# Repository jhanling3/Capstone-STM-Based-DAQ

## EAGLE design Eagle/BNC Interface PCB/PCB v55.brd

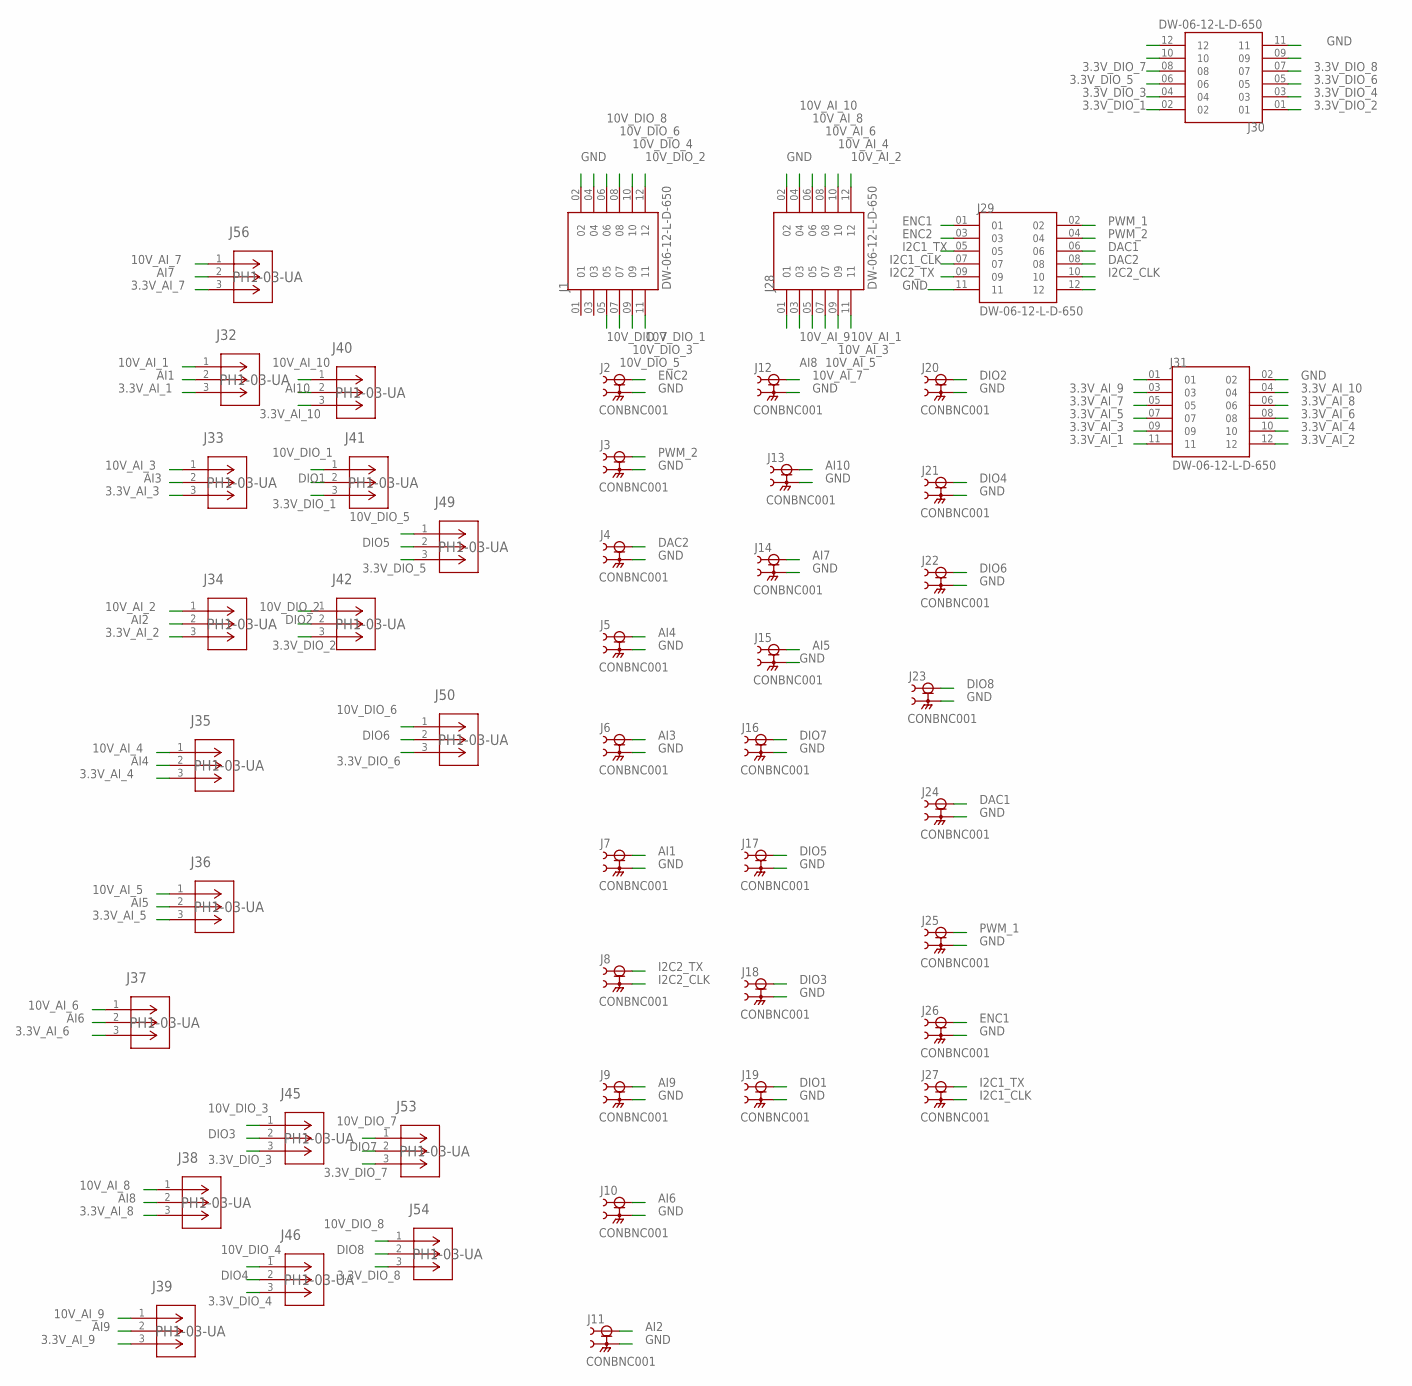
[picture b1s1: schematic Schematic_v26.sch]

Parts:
J1, J28, J29, J30, J31: DW-06-12-L-D-650; SAMTEC_DW-06-12-L-D-650
J2, J3, J4, J5, J6, J7, J8, J9, J10, J11, J12, J13, J14, J15, J16, J17, J18, J19, J20, J21, J22, J23, J24, J25, J26, J27: CONBNC001; LINX_CONBNC001
J32, J33, J34, J35, J36, J37, J38, J39, J40, J41, J42, J45, J46, J49, J50, J53, J54, J56: PH1-03-UA; CONN_PH1-03-UA_ADM

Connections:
3.3V_AI_1: J31.11, J32.3
3.3V_AI_2: J31.12, J34.3
3.3V_AI_3: J31.09, J33.3
3.3V_AI_4: J31.10, J35.3
3.3V_AI_5: J31.07, J36.3
3.3V_AI_6: J31.08, J37.3
3.3V_AI_7: J31.05, J56.3
3.3V_AI_8: J31.06, J38.3
3.3V_AI_9: J31.03, J39.3
3.3V_AI_10: J31.04, J40.3
3.3V_DIO_1: J30.02, J41.3
3.3V_DIO_2: J30.01, J42.3
3.3V_DIO_3: J30.04, J45.3
3.3V_DIO_4: J30.03, J46.3
3.3V_DIO_5: J30.06, J49.3
3.3V_DIO_6: J30.05, J50.3
3.3V_DIO_7: J30.08, J53.3
3.3V_DIO_8: J30.07, J54.3
10V_AI_1: J28.11, J32.1
10V_AI_2: J28.12, J34.1
10V_AI_3: J28.09, J33.1
10V_AI_4: J28.10, J35.1
10V_AI_5: J28.07, J36.1
10V_AI_6: J28.08, J37.1
10V_AI_7: J28.05, J56.1
10V_AI_8: J28.06, J38.1
10V_AI_9: J28.03, J39.1
10V_AI_10: J28.04, J40.1
10V_DIO_1: J1.11, J41.1
10V_DIO_2: J1.12, J42.1
10V_DIO_3: J1.09, J45.1
10V_DIO_4: J1.10, J46.1
10V_DIO_5: J1.07, J49.1
10V_DIO_6: J1.08, J50.1
10V_DIO_7: J1.05, J53.1
10V_DIO_8: J1.06, J54.1
AI1: J7.1, J32.2
AI2: J11.1, J34.2
AI3: J6.1, J33.2
AI4: J5.1, J35.2
AI5: J15.1, J36.2
AI6: J10.1, J37.2
AI7: J14.1, J56.2
AI8: J12.1, J38.2
AI9: J9.1, J39.2
AI10: J13.1, J40.2
DAC1: J24.1, J29.06
DAC2: J4.1, J29.08
DIO1: J19.1, J41.2
DIO2: J20.1, J42.2
DIO3: J18.1, J45.2
DIO4: J21.1, J46.2
DIO5: J17.1, J49.2
DIO6: J22.1, J50.2
DIO7: J16.1, J53.2
DIO8: J23.1, J54.2
ENC1: J26.1, J29.01
ENC2: J2.1, J29.03
GND: J1.02, J2.S1 (2), J2.S2 (2), J2.S3 (2), J2.S4 (2), J3.S1 (2), J3.S2 (2), J3.S3 (2), J3.S4 (2), J4.S1 (2), J4.S2 (2), J4.S3 (2), J4.S4 (2), J5.S1 (2), J5.S2 (2), J5.S3 (2), J5.S4 (2), J6.S1 (2), J6.S2 (2), J6.S3 (2), J6.S4 (2), J7.S1 (2), J7.S2 (2), J7.S3 (2), J7.S4 (2), J9.S1 (2), J9.S2 (2), J9.S3 (2), J9.S4 (2), J10.S1 (2), J10.S2 (2), J10.S3 (2), J10.S4 (2), J11.S1 (2), J11.S2 (2), J11.S3 (2), J11.S4 (2), J12.S1 (2), J12.S2 (2), J12.S3 (2), J12.S4 (2), J13.S1 (2), J13.S2 (2), J13.S3 (2), J13.S4 (2), J14.S1 (2), J14.S2 (2), J14.S3 (2), J14.S4 (2), J15.S1 (2), J15.S2 (2), J15.S3 (2), J15.S4 (2), J16.S1 (2), J16.S2 (2), J16.S3 (2), J16.S4 (2), J17.S1 (2), J17.S2 (2), J17.S3 (2), J17.S4 (2), J18.S1 (2), J18.S2 (2), J18.S3 (2), J18.S4 (2), J19.S1 (2), J19.S2 (2), J19.S3 (2), J19.S4 (2), J20.S1 (2), J20.S2 (2), J20.S3 (2), J20.S4 (2), J21.S1 (2), J21.S2 (2), J21.S3 (2), J21.S4 (2), J22.S1 (2), J22.S2 (2), J22.S3 (2), J22.S4 (2), J23.S1 (2), J23.S2 (2), J23.S3 (2), J23.S4 (2), J24.S1 (2), J24.S2 (2), J24.S3 (2), J24.S4 (2), J25.S1 (2), J25.S2 (2), J25.S3 (2), J25.S4 (2), J26.S1 (2), J26.S2 (2), J26.S3 (2), J26.S4 (2), J28.02, J29.11, J30.11, J31.02
I2C1_CLK: J27.S1 (2), J27.S2 (2), J27.S3 (2), J27.S4 (2), J29.07
I2C1_TX: J27.1, J29.05
I2C2_CLK: J8.S1 (2), J8.S2 (2), J8.S3 (2), J8.S4 (2), J29.10
I2C2_TX: J8.1, J29.09
PWM_1: J25.1, J29.02
PWM_2: J3.1, J29.04

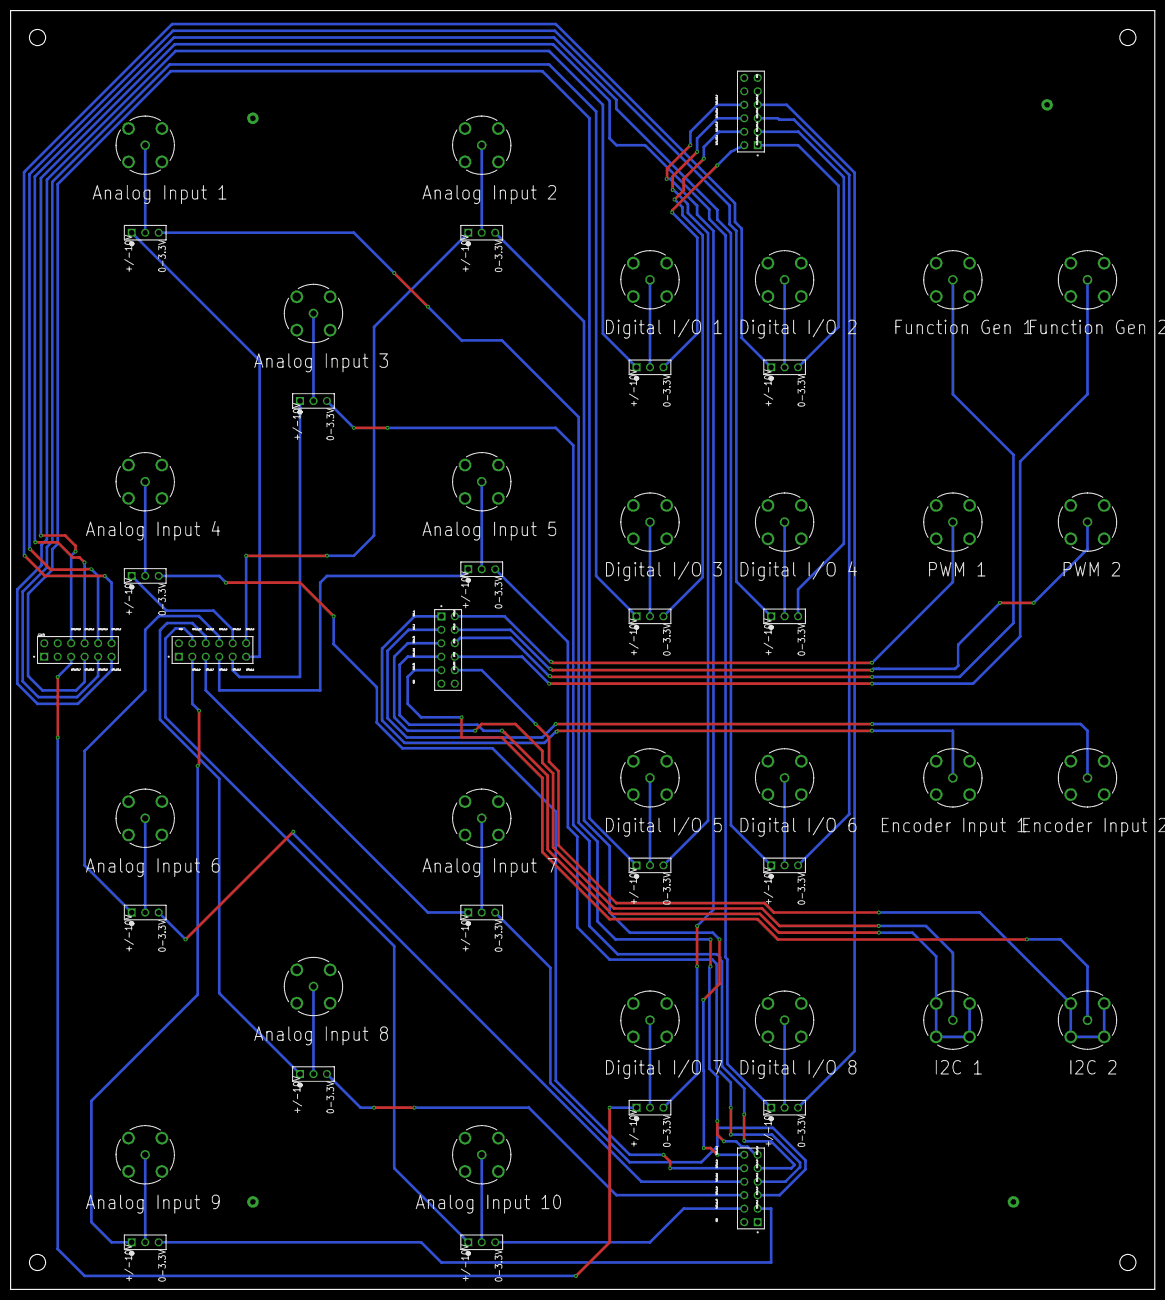
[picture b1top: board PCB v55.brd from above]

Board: 2 copper layers, 215.9 x 241.3 mm, 49 parts (0 on the bottom side), 65 nets.

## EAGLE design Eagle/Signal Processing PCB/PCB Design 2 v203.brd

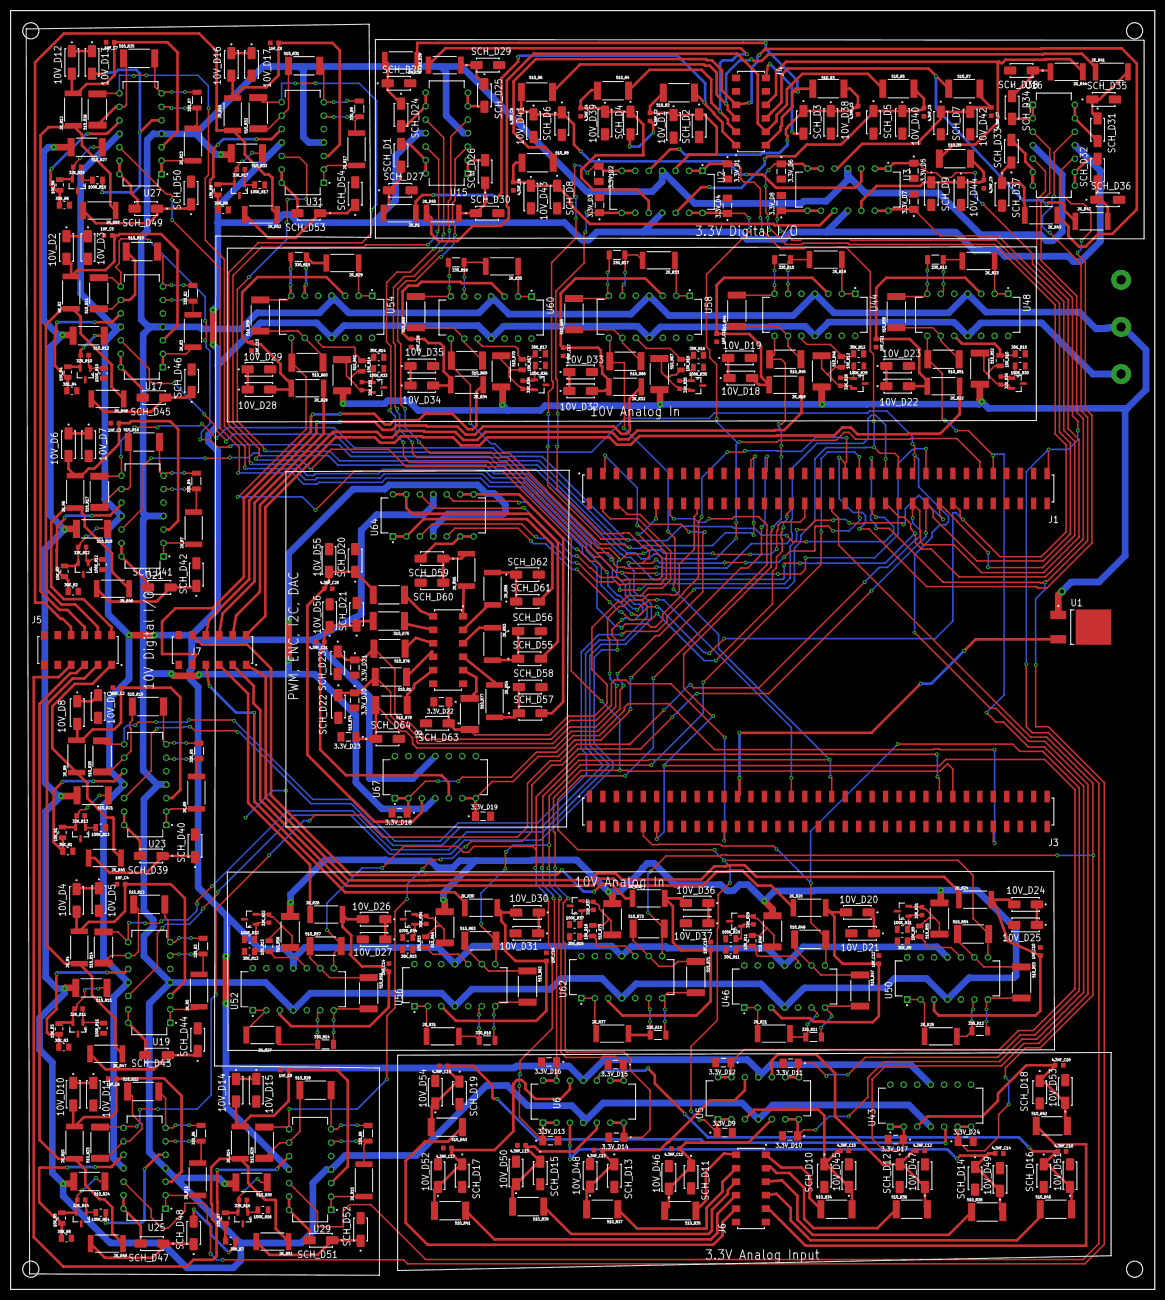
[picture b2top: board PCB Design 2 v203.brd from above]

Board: 2 copper layers, 215.9 x 241.3 mm, 459 parts (0 on the bottom side), 308 nets.

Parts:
1NF_C2, 1NF_C3, 1NF_C4, 1NF_C5, 1NF_C6, 1NF_C7, 1NF_C8, 1NF_C9, 1NF_C10, 1NF_C11, 1NF_C12, 1NF_C13, 1NF_C14, 1NF_C15, 1NF_C16, 1NF_C17, 1NF_C18, 1NF_C19: GRM1885C1H102JA01D; CAPC1608X90N
2K_R1, 2K_R2, 2K_R3, 2K_R4, 2K_R5, 2K_R6, 2K_R7, 2K_R8, 2K_R9, 2K_R10, 2K_R11, 2K_R12, 2K_R13, 2K_R14, 2K_R15, 2K_R16, 2K_R17, 2K_R18, 2K_R19, 2K_R20, 2K_R21, 2K_R22, 2K_R23, 2K_R24, 2K_R25, 2K_R26, 2K_R27, 2K_R28, 2K_R29, 2K_R30, 2K_R31, 2K_R32, 2K_R33, 2K_R34, 2K_R35, 2K_R36, 2K_R37, 2K_R38, 2K_R39, 2K_R40, 2K_R41, 2K_R42, 2K_R43, 2K_R44, 2K_R45, 2K_R46, 2K_R47, 2K_R48, 2K_R49, 2K_R50, 2K_R51, 2K_R52, 2K_R53, 2K_R54, 2K_R55, 2K_R56: RC2512FK-072KL; RESC6331X65N
3.3V_D1, 3.3V_D2, 3.3V_D3, 3.3V_D4, 3.3V_D5, 3.3V_D6, 3.3V_D7, 3.3V_D8, 3.3V_D9, 3.3V_D10, 3.3V_D11, 3.3V_D12, 3.3V_D13, 3.3V_D14, 3.3V_D15, 3.3V_D16, 3.3V_D17, 3.3V_D18, 3.3V_D19, 3.3V_D20, 3.3V_D21, 3.3V_D22, 3.3V_D23, 3.3V_D24: BZT52B3V3_RHG; DIO_BZT52B3V3_RHG
4.3NF_C2, 4.3NF_C3, 4.3NF_C4, 4.3NF_C5, 4.3NF_C6, 4.3NF_C7, 4.3NF_C8, 4.3NF_C9, 4.3NF_C10, 4.3NF_C11, 4.3NF_C12, 4.3NF_C13, 4.3NF_C14, 4.3NF_C15, 4.3NF_C16, 4.3NF_C17, 4.3NF_C18, 4.3NF_C19, 4.3NF_C20, 4.3NF_C21: GRM1885C1H432JA01D; CAPC1608X90N
10K_R1, 10K_R2, 10K_R3, 10K_R4, 10K_R5, 10K_R6, 10K_R7, 10K_R8, 10K_R9, 10K_R10, 10K_R11, 10K_R12, 10K_R13, 10K_R14, 10K_R15, 10K_R16, 10K_R17, 10K_R18: RCS080510K0FKEA; RESC2012X50N
10V_D1, 10V_D2, 10V_D3, 10V_D4, 10V_D5, 10V_D6, 10V_D7, 10V_D8, 10V_D9, 10V_D10, 10V_D11, 10V_D12, 10V_D13, 10V_D14, 10V_D15, 10V_D16, 10V_D17, 10V_D18, 10V_D19, 10V_D20, 10V_D21, 10V_D22, 10V_D23, 10V_D24, 10V_D25, 10V_D26, 10V_D27, 10V_D28, 10V_D29, 10V_D30, 10V_D31, 10V_D32, 10V_D33, 10V_D34, 10V_D35, 10V_D36, 10V_D37, 10V_D38, 10V_D39, 10V_D40, 10V_D41, 10V_D42, 10V_D43, 10V_D44, 10V_D45, 10V_D46, 10V_D47, 10V_D48, 10V_D49, 10V_D50, 10V_D51, 10V_D52, 10V_D53, 10V_D54, 10V_D55, 10V_D56: SMAZ10-13-F; DIOM5226X240N
30K_R1, 30K_R2, 30K_R3, 30K_R4, 30K_R5, 30K_R6, 30K_R7, 30K_R8, 30K_R9, 30K_R10, 30K_R11, 30K_R12, 30K_R13, 30K_R14, 30K_R15, 30K_R16, 30K_R17, 30K_R18: RMCF0805FT30K0; RESC2012X65N
32K_R10, 32K_R11, 32K_R12, 32K_R13, 32K_R14, 32K_R15, 32K_R16, 32K_R17, 32K_R28, 32K_R29, 32K_R30, 32K_R31, 32K_R32, 32K_R33, 32K_R34, 32K_R35, 32K_R36, 32K_R37: RNCF0603BTE32K0; RESC1508X55N
100K_R10, 100K_R11, 100K_R12, 100K_R13, 100K_R14, 100K_R15, 100K_R16, 100K_R17, 100K_R28, 100K_R29, 100K_R30, 100K_R31, 100K_R32, 100K_R33, 100K_R34, 100K_R35, 100K_R36, 100K_R37: RC0805FR-07100KL; RESC2012X60N
330_R2, 330_R3, 330_R4, 330_R5, 330_R6, 330_R7, 330_R8, 330_R9, 330_R10, 330_R11, 330_R12, 330_R13, 330_R14, 330_R15, 330_R16, 330_R17, 330_R18, 330_R19: RC1206FR-07330RL; RESC3116X65N
510_R1, 510_R2, 510_R3, 510_R4, 510_R5, 510_R6, 510_R7, 510_R8, 510_R9, 510_R10, 510_R11, 510_R12, 510_R13, 510_R14, 510_R15, 510_R16, 510_R17, 510_R18, 510_R19, 510_R20, 510_R21, 510_R22, 510_R23, 510_R24, 510_R25, 510_R26, 510_R27, 510_R28, 510_R29, 510_R30, 510_R31, 510_R32, 510_R33, 510_R34, 510_R35, 510_R36, 510_R37, 510_R38, 510_R39, 510_R40, 510_R41, 510_R42, 510_R43, 510_R44, 510_R45, 510_R46, 510_R47, 510_R48, 510_R49, 510_R50, 510_R51, 510_R52, 510_R53, 510_R54, 510_R55, 510_R56, 510_R57, 510_R58, 510_R59, 510_R60, 510_R61, 510_R62, 510_R63, 510_R64, 510_R65, 510_R66, 510_R67, 510_R68, 510_R69, 510_R70, 510_R71, 510_R72, 510_R73, 510_R74, 510_R75, 510_R76, 510_R77, 510_R78: RMCF2512FT510R; RESC6332X70N
J1, J3: SSM-135-L-DV; SAMTEC_SSM-135-L-DV
J4, J5, J6, J7, J8: 89898-306ALF; AMPHENOL_89898-306ALF
SCH_D1, SCH_D2, SCH_D3, SCH_D4, SCH_D5, SCH_D6, SCH_D7, SCH_D8, SCH_D9, SCH_D10, SCH_D11, SCH_D12, SCH_D13, SCH_D14, SCH_D15, SCH_D16, SCH_D17, SCH_D18, SCH_D19, SCH_D20, SCH_D21, SCH_D22, SCH_D23, SCH_D24, SCH_D25, SCH_D26, SCH_D27, SCH_D28, SCH_D29, SCH_D30, SCH_D31, SCH_D32, SCH_D33, SCH_D34, SCH_D35, SCH_D36, SCH_D37, SCH_D38, SCH_D39, SCH_D40, SCH_D41, SCH_D42, SCH_D43, SCH_D44, SCH_D45, SCH_D46, SCH_D47, SCH_D48, SCH_D49, SCH_D50, SCH_D51, SCH_D52, SCH_D53, SCH_D54, SCH_D55, SCH_D56, SCH_D57, SCH_D58, SCH_D59, SCH_D60, SCH_D61, SCH_D62, SCH_D63, SCH_D64: B140-13-F; DIOM4326X240N
U1: L78M08CDT-TR; VREG_L78M08CDT-TR
U2, U3, U5, U6, U15, U16, U17, U19, U21, U23, U25, U27, U29, U31, U43, U44, U46, U48, U50, U52, U54, U56, U58, U60, U62, U64, U67: TL074IN; DIP794W45P254L1969H508Q14
U18, U20, U22, U24, U26, U28, U30, U32, U45, U47, U49, U51, U53, U55, U57, U59, U61, U63: TL431AIDBZR; SOT95P237X112-3N

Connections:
3.3_AI_1: 510_R34.1, J6.01
3.3_AI_2: 510_R35.1, J6.02
3.3_AI_3: 510_R36.1, J6.03
3.3_AI_4: 510_R37.1, J6.04
3.3_AI_5: 510_R38.1, J6.05
3.3_AI_6: 510_R39.1, J6.06
3.3_AI_7: 510_R40.1, J6.07
3.3_AI_8: 510_R41.1, J6.08
3.3_AI_9: 510_R42.1, J6.09
3.3_AI_10: 510_R43.1, J6.10
10V_AI_1: 2K_R24.1, J7.01
10V_AI_2: 2K_R22.1, J7.02
10V_AI_3: 2K_R20.1, J7.03
10V_AI_4: 2K_R18.1, J7.04
10V_AI_5: 2K_R26.1, J7.05
10V_AI_6: 2K_R28.1, J7.06
10V_AI_7: 2K_R30.1, J7.07
10V_AI_8: 2K_R32.1, J7.08
10V_AI_9: 2K_R34.1, J7.09
10V_AI_10: 2K_R36.1, J7.10
10V_DIO_1: 2K_R8.1, 2K_R45.1, J5.01
10V_DIO_1_PRE: SCH_D39.A, U23.13, U23.14
10V_DIO_2: 2K_R6.1, 2K_R46.1, J5.02
10V_DIO_3: 2K_R4.1, 2K_R47.1, J5.03
10V_DIO_3_PRE: SCH_D43.A, U19.13, U19.14
10V_DIO_4: 2K_R2.1, 2K_R48.1, J5.04
10V_DIO_4_PRE: SCH_D45.A, U17.13, U17.14
10V_DIO_5: 2K_R10.1, 2K_R49.1, J5.05
10V_DIO_5_PRE: SCH_D47.A, U25.13, U25.14
10V_DIO_6: 2K_R12.1, 2K_R50.1, J5.06
10V_DIO_6_PRE: SCH_D49.A, U27.13, U27.14
10V_DIO_7: 2K_R14.1, 2K_R51.1, J5.07
10V_DIO_7_PRE: SCH_D51.A, U29.13, U29.14
10V_DIO_8: 2K_R16.1, 2K_R52.1, J5.08
10V_DIO_8_PRE: SCH_D53.A, U31.13, U31.14
10V_DIO_PRE: SCH_D41.A, U21.13, U21.14
+V: 510_R12.2, 510_R15.2, 510_R18.2, 510_R21.2, 510_R24.2, 510_R27.2, 510_R30.2, 510_R33.2, 510_R46.2, 510_R49.2, 510_R52.2, 510_R55.2, 510_R58.2, 510_R61.2, 510_R64.2, 510_R67.2, 510_R70.2, 510_R73.2, U1.1, U2.4, U3.4, U5.4, U6.4, U15.4, U16.4, U17.4, U19.4, U21.4, U23.4, U25.4, U27.4, U29.4, U31.4, U43.4, U44.4, U46.4, U48.4, U50.4, U52.4, U54.4, U56.4, U58.4, U60.4, U62.4, U64.4, U67.4
-V: U2.11, U3.11, U5.11, U6.11, U15.11, U16.11, U17.11, U19.11, U21.11, U23.11, U25.11, U27.11, U29.11, U31.11, U43.11, U44.11, U46.11, U48.11, U50.11, U52.11, U54.11, U56.11, U58.11, U60.11, U62.11, U64.11, U67.11
AI_AMP_1: 4.3NF_C10.1, 10V_D45.1, 510_R34.2, SCH_D10.C, U5.3
AI_AMP_2: 4.3NF_C11.1, 10V_D46.1, 510_R35.2, SCH_D11.C, U5.5
AI_AMP_3: 4.3NF_C12.1, 10V_D47.1, 510_R36.2, SCH_D12.C, U5.10
AI_AMP_4: 4.3NF_C13.1, 10V_D48.1, 510_R37.2, SCH_D13.C, U5.12
AI_AMP_5: 4.3NF_C14.1, 10V_D49.1, 510_R38.2, SCH_D14.C, U6.3
AI_AMP_6: 4.3NF_C15.1, 10V_D50.1, 510_R39.2, SCH_D15.C, U6.5
AI_AMP_7: 4.3NF_C16.1, 10V_D51.1, 510_R40.2, SCH_D16.C, U6.10
AI_AMP_8: 4.3NF_C17.1, 10V_D52.1, 510_R41.2, SCH_D17.C, U6.12
AI_AMP_9: 4.3NF_C18.1, 10V_D53.1, 510_R42.2, SCH_D18.C, U43.3
AI_AMP_10: 4.3NF_C19.1, 10V_D54.1, 510_R43.2, SCH_D19.C, U43.5
DAC1: 2K_R53.1, J8.05
DAC1_T: SCH_D57.A, U64.8, U64.9
DAC2: 2K_R54.1, J8.07
DAC2_T: SCH_D55.A, U64.13, U64.14
DIO_1: 2K_R1.1, 510_R2.1, J4.01
DIO_1_T: SCH_D1.A, U15.13, U15.14
DIO_2: 2K_R38.1, 510_R3.1, J4.02
DIO_2_T: SCH_D24.A, U15.8, U15.9
DIO_3: 2K_R39.1, 510_R4.1, J4.03
DIO_3_T: SCH_D25.A, U15.6, U15.7
DIO_4: 2K_R40.1, 510_R5.1, J4.04
DIO_4_T: SCH_D26.A, U15.1, U15.2
DIO_5: 2K_R41.1, 510_R6.1, J4.05
DIO_5_T: SCH_D31.A, U16.13, U16.14
DIO_6: 2K_R42.1, 510_R7.1, J4.06
DIO_6_T: SCH_D32.A, U16.8, U16.9
DIO_7: 2K_R43.1, 510_R8.1, J4.07
DIO_7_T: SCH_D33.A, U16.6, U16.7
DIO_8: 2K_R44.1, 510_R9.1, J4.08
DIO_8_T: SCH_D34.A, U16.1, U16.2
DIO_AMP_1: 4.3NF_C2.1, 10V_D1.1, 510_R2.2, SCH_D2.C, U2.3
DIO_AMP_2: 4.3NF_C3.1, 10V_D38.1, 510_R3.2, SCH_D3.C, U2.5
DIO_AMP_3: 4.3NF_C4.1, 10V_D39.1, 510_R4.2, SCH_D4.C, U2.10
DIO_AMP_4: 4.3NF_C5.1, 10V_D40.1, 510_R5.2, SCH_D5.C, U2.12
DIO_AMP_5: 4.3NF_C6.1, 10V_D41.1, 510_R6.2, SCH_D6.C, U3.3
DIO_AMP_6: 4.3NF_C7.1, 10V_D42.1, 510_R7.2, SCH_D7.C, U3.5
DIO_AMP_7: 4.3NF_C8.1, 10V_D43.1, 510_R8.2, SCH_D8.C, U3.10
DIO_AMP_8: 4.3NF_C9.1, 10V_D44.1, 510_R9.2, SCH_D9.C, U3.12
ENC_1: 510_R74.1, J8.02
ENC_2: 510_R75.1, J8.04
ENC_AMP_1: 4.3NF_C20.1, 10V_D55.1, 510_R74.2, SCH_D20.C, U67.3
ENC_AMP_2: 4.3NF_C21.1, 10V_D56.1, 510_R75.2, SCH_D21.C, U67.5
GND: 1NF_C2.2, 1NF_C3.2, 1NF_C4.2, 1NF_C5.2, 1NF_C6.2, 1NF_C7.2, 1NF_C8.2, 1NF_C9.2, 1NF_C10.2, 1NF_C11.2, 1NF_C12.2, 1NF_C13.2, 1NF_C14.2, 1NF_C15.2, 1NF_C16.2, 1NF_C17.2, 1NF_C18.2, 1NF_C19.2, 3.3V_D1.A, 3.3V_D2.A, 3.3V_D3.A, 3.3V_D4.A, 3.3V_D5.A, 3.3V_D6.A, 3.3V_D7.A, 3.3V_D8.A, 3.3V_D9.A, 3.3V_D10.A, 3.3V_D11.A, 3.3V_D12.A, 3.3V_D13.A, 3.3V_D14.A, 3.3V_D15.A, 3.3V_D16.A, 3.3V_D17.A, 3.3V_D18.A, 3.3V_D19.A, 3.3V_D20.A, 3.3V_D21.A, 3.3V_D22.A, 3.3V_D23.A, 3.3V_D24.A, 4.3NF_C2.2, 4.3NF_C3.2, 4.3NF_C4.2, 4.3NF_C5.2, 4.3NF_C6.2, 4.3NF_C7.2, 4.3NF_C8.2, 4.3NF_C9.2, 4.3NF_C10.2, 4.3NF_C11.2, 4.3NF_C12.2, 4.3NF_C13.2, 4.3NF_C14.2, 4.3NF_C15.2, 4.3NF_C16.2, 4.3NF_C17.2, 4.3NF_C18.2, 4.3NF_C19.2, 4.3NF_C20.2, 4.3NF_C21.2, 10V_D1.2, 10V_D3.2, 10V_D5.2, 10V_D7.2, 10V_D9.2, 10V_D11.2, 10V_D13.2, 10V_D15.2, 10V_D17.2, 10V_D19.2, 10V_D21.2, 10V_D23.2, 10V_D25.2, 10V_D27.2, 10V_D29.2, 10V_D31.2, 10V_D33.2, 10V_D35.2, 10V_D37.2, 10V_D38.2, 10V_D39.2, 10V_D40.2, 10V_D41.2, 10V_D42.2, 10V_D43.2, 10V_D44.2, 10V_D45.2, 10V_D46.2, 10V_D47.2, 10V_D48.2, 10V_D49.2, 10V_D50.2, 10V_D51.2, 10V_D52.2, 10V_D53.2, 10V_D54.2, 10V_D55.2, 10V_D56.2, 30K_R1.2, 30K_R2.2, 30K_R3.2, 30K_R4.2, 30K_R5.2, 30K_R6.2, 30K_R7.2, 30K_R8.2, 30K_R9.2, 30K_R10.2, 30K_R11.2, 30K_R12.2, 30K_R13.2, 30K_R14.2, 30K_R15.2, 30K_R16.2, 30K_R17.2, 30K_R18.2, 100K_R10.1, 100K_R11.1, 100K_R12.1, 100K_R13.1, 100K_R14.1, 100K_R15.1, 100K_R16.1, 100K_R17.1, 100K_R28.1, 100K_R29.1, 100K_R30.1, 100K_R31.1, 100K_R32.1, 100K_R33.1, 100K_R34.1, 100K_R35.1, 100K_R36.1, 100K_R37.1, J1.10, J1.19, J1.40, J1.53, J1.64, J3.07, J3.19, J3.20, J3.21, J3.50, J3.59, J4.12, J5.12, J6.12, J7.12, J8.12, SCH_D2.A, SCH_D3.A, SCH_D4.A, SCH_D5.A, SCH_D6.A, SCH_D7.A, SCH_D8.A, SCH_D9.A, SCH_D10.A, SCH_D11.A, SCH_D12.A, SCH_D13.A, SCH_D14.A, SCH_D15.A, SCH_D16.A, SCH_D17.A, SCH_D18.A, SCH_D19.A, SCH_D20.A, SCH_D21.A, SCH_D22.A, SCH_D23.A, SCH_D27.A, SCH_D28.A, SCH_D29.A, SCH_D30.A, SCH_D35.A, SCH_D36.A, SCH_D37.A, SCH_D38.A, SCH_D40.A, SCH_D42.A, SCH_D44.A, SCH_D46.A, SCH_D48.A, SCH_D50.A, SCH_D52.A, SCH_D54.A, SCH_D56.A, SCH_D58.A, SCH_D60.A, SCH_D62.A, SCH_D63.A, SCH_D64.A, U1.2, U17.5, U18.3, U19.5, U20.3, U21.5, U22.3, U23.5, U24.3, U25.5, U26.3, U27.5, U28.3, U29.5, U30.3, U31.5, U32.3, U44.5, U45.3, U46.5, U47.3, U48.5, U49.3, U50.5, U51.3, U52.5, U53.3, U54.5, U55.3, U56.5, U57.3, U58.5, U59.3, U60.5, U61.3, U62.5, U63.3
I2C1_CLK: 510_R1.1, J8.08
I2C1_TX: 510_R76.1, J8.06
I2C2_CLK: 510_R77.1, J8.09
I2C2_TX: 510_R78.1, J8.10
unnamed: 2K_R1.2, SCH_D1.C, SCH_D27.C
unnamed: 2K_R38.2, SCH_D24.C, SCH_D28.C
unnamed: 2K_R39.2, SCH_D25.C, SCH_D29.C
unnamed: 2K_R40.2, SCH_D26.C, SCH_D30.C
unnamed: 2K_R41.2, SCH_D31.C, SCH_D35.C
unnamed: 1NF_C5.1, 2K_R2.2, 10V_D2.2, U17.3
unnamed: 10V_D2.1, 10V_D3.1
unnamed: 2K_R43.2, SCH_D33.C, SCH_D37.C
unnamed: 2K_R3.1, U17.1, U17.2
unnamed: 2K_R44.2, SCH_D34.C, SCH_D38.C
unnamed: 2K_R42.2, SCH_D32.C, SCH_D36.C
unnamed: 510_R10.1, 510_R11.1, U17.9
unnamed: 330_R2.2, 510_R10.2, U17.7
unnamed: 2K_R3.2, 330_R2.1, U17.6
unnamed: 32K_R10.1, 100K_R10.2, U18.1
unnamed: 10K_R5.2, 32K_R14.2, 510_R24.1, U26.2
unnamed: 1NF_C4.1, 2K_R4.2, 10V_D4.2, U19.3
unnamed: 10V_D4.1, 10V_D5.1
unnamed: 2K_R5.1, U19.1, U19.2
unnamed: 330_R3.2, 510_R13.2, U19.7
unnamed: 2K_R5.2, 330_R3.1, U19.6
unnamed: 510_R13.1, 510_R14.1, U19.9
unnamed: 32K_R11.1, 100K_R11.2, U20.1
unnamed: 10K_R4.2, 32K_R10.2, 510_R12.1, U18.2
unnamed: 1NF_C3.1, 2K_R6.2, 10V_D6.2, U21.3
unnamed: 10V_D6.1, 10V_D7.1
unnamed: 2K_R7.1, U21.1, U21.2
unnamed: 330_R4.2, 510_R16.2, U21.7
unnamed: 2K_R7.2, 330_R4.1, U21.6
unnamed: 510_R16.1, 510_R17.1, U21.9
unnamed: 32K_R12.1, 100K_R12.2, U22.1
unnamed: 10K_R3.2, 32K_R11.2, 510_R15.1, U20.2
unnamed: 1NF_C2.1, 2K_R8.2, 10V_D8.2, U23.3
unnamed: 10V_D8.1, 10V_D9.1
unnamed: 2K_R9.1, U23.1, U23.2
unnamed: 330_R5.2, 510_R19.2, U23.7
unnamed: 2K_R9.2, 330_R5.1, U23.6
unnamed: 510_R19.1, 510_R20.1, U23.9
unnamed: 32K_R13.1, 100K_R13.2, U24.1
unnamed: 2K_R45.2, SCH_D39.C, SCH_D40.C
unnamed: 1NF_C6.1, 2K_R10.2, 10V_D10.2, U25.3
unnamed: 10V_D10.1, 10V_D11.1
unnamed: 2K_R11.1, U25.1, U25.2
unnamed: 330_R6.2, 510_R22.2, U25.7
unnamed: 2K_R11.2, 330_R6.1, U25.6
unnamed: 510_R22.1, 510_R23.1, U25.9
unnamed: 32K_R14.1, 100K_R14.2, U26.1
unnamed: 10K_R6.2, 32K_R15.2, 510_R27.1, U28.2
unnamed: 1NF_C7.1, 2K_R12.2, 10V_D12.2, U27.3
unnamed: 10V_D12.1, 10V_D13.1
unnamed: 2K_R13.1, U27.1, U27.2
unnamed: 330_R7.2, 510_R25.2, U27.7
unnamed: 2K_R13.2, 330_R7.1, U27.6
unnamed: 510_R25.1, 510_R26.1, U27.9
unnamed: 32K_R15.1, 100K_R15.2, U28.1
unnamed: 10K_R7.2, 32K_R16.2, 510_R30.1, U30.2
unnamed: 2K_R53.2, SCH_D55.C, SCH_D56.C
unnamed: 1NF_C13.1, 2K_R18.2, 10V_D18.2, U44.3
unnamed: 1NF_C8.1, 2K_R14.2, 10V_D14.2, U29.3
unnamed: 10V_D14.1, 10V_D15.1
unnamed: 2K_R15.1, U29.1, U29.2
unnamed: 330_R8.2, 510_R28.2, U29.7
unnamed: 2K_R15.2, 330_R8.1, U29.6
unnamed: 510_R28.1, 510_R29.1, U29.9
unnamed: 10V_D18.1, 10V_D19.1
unnamed: 32K_R16.1, 100K_R16.2, U30.1
unnamed: 10K_R8.2, 32K_R17.2, 510_R33.1, U32.2
unnamed: 1NF_C9.1, 2K_R16.2, 10V_D16.2, U31.3
unnamed: 10V_D16.1, 10V_D17.1
unnamed: 2K_R17.1, U31.1, U31.2
unnamed: 330_R9.2, 510_R31.2, U31.7
unnamed: 2K_R17.2, 330_R9.1, U31.6
unnamed: 510_R31.1, 510_R32.1, U31.9
unnamed: 2K_R19.1, U44.1, U44.2
unnamed: 32K_R17.1, 100K_R17.2, U32.1
unnamed: 10K_R15.2, 32K_R34.2, 510_R64.1, U57.2
unnamed: 330_R10.2, 510_R44.2, U44.7
unnamed: 2K_R19.2, 330_R10.1, U44.6
unnamed: 510_R44.1, 510_R45.1, U44.9
unnamed: 32K_R28.1, 100K_R28.2, U45.1
unnamed: 10K_R13.1, 30K_R13.1, U52.10
unnamed: 1NF_C12.1, 2K_R20.2, 10V_D20.2, U46.3
unnamed: 10V_D20.1, 10V_D21.1
unnamed: 2K_R21.1, U46.1, U46.2
unnamed: 330_R11.2, 510_R47.2, U46.7
unnamed: 2K_R21.2, 330_R11.1, U46.6
unnamed: 510_R47.1, 510_R48.1, U46.9
unnamed: 32K_R29.1, 100K_R29.2, U47.1
unnamed: 10K_R12.1, 30K_R12.1, U44.10
unnamed: 1NF_C11.1, 2K_R22.2, 10V_D22.2, U48.3
unnamed: 10V_D22.1, 10V_D23.1
unnamed: 2K_R23.1, U48.1, U48.2
unnamed: 330_R12.2, 510_R50.2, U48.7
unnamed: 2K_R23.2, 330_R12.1, U48.6
unnamed: 510_R50.1, 510_R51.1, U48.9
unnamed: 32K_R30.1, 100K_R30.2, U49.1
unnamed: 10K_R11.1, 30K_R11.1, U46.10
unnamed: 1NF_C10.1, 2K_R24.2, 10V_D24.2, U50.3
unnamed: 10V_D24.1, 10V_D25.1
unnamed: 2K_R25.1, U50.1, U50.2
unnamed: 330_R13.2, 510_R53.2, U50.7
unnamed: 2K_R25.2, 330_R13.1, U50.6
unnamed: 510_R53.1, 510_R54.1, U50.9
unnamed: 32K_R31.1, 100K_R31.2, U51.1
unnamed: 10K_R10.1, 30K_R10.1, U48.10
unnamed: 10K_R9.1, 30K_R9.1, U50.10
unnamed: 1NF_C14.1, 2K_R26.2, 10V_D26.2, U52.3
unnamed: 10V_D26.1, 10V_D27.1
unnamed: 2K_R27.1, U52.1, U52.2
unnamed: 330_R14.2, 510_R56.2, U52.7
unnamed: 2K_R27.2, 330_R14.1, U52.6
unnamed: 510_R56.1, 510_R57.1, U52.9
unnamed: 32K_R32.1, 100K_R32.2, U53.1
unnamed: 10K_R14.1, 30K_R14.1, U54.10
unnamed: 1NF_C15.1, 2K_R28.2, 10V_D28.2, U54.3
unnamed: 10V_D28.1, 10V_D29.1
unnamed: 2K_R29.1, U54.1, U54.2
unnamed: 330_R15.2, 510_R59.2, U54.7
unnamed: 2K_R29.2, 330_R15.1, U54.6
unnamed: 510_R59.1, 510_R60.1, U54.9
unnamed: 32K_R33.1, 100K_R33.2, U55.1
unnamed: 2K_R46.2, SCH_D41.C, SCH_D42.C
unnamed: 1NF_C16.1, 2K_R30.2, 10V_D30.2, U56.3
unnamed: 10V_D30.1, 10V_D31.1
unnamed: 2K_R31.1, U56.1, U56.2
unnamed: 330_R16.2, 510_R62.2, U56.7
unnamed: 2K_R31.2, 330_R16.1, U56.6
unnamed: 510_R62.1, 510_R63.1, U56.9
unnamed: 32K_R34.1, 100K_R34.2, U57.1
unnamed: 10K_R16.1, 30K_R16.1, U58.10
unnamed: 1NF_C17.1, 2K_R32.2, 10V_D32.2, U58.3
unnamed: 10V_D32.1, 10V_D33.1
unnamed: 2K_R33.1, U58.1, U58.2
unnamed: 330_R17.2, 510_R65.2, U58.7
unnamed: 2K_R33.2, 330_R17.1, U58.6
unnamed: 510_R65.1, 510_R66.1, U58.9
unnamed: 32K_R35.1, 100K_R35.2, U59.1
unnamed: 10K_R17.1, 30K_R17.1, U60.10
unnamed: 1NF_C18.1, 2K_R34.2, 10V_D34.2, U60.3
unnamed: 10V_D34.1, 10V_D35.1
unnamed: 2K_R35.1, U60.1, U60.2
unnamed: 330_R18.2, 510_R68.2, U60.7
unnamed: 2K_R35.2, 330_R18.1, U60.6
unnamed: 510_R68.1, 510_R69.1, U60.9
unnamed: 32K_R36.1, 100K_R36.2, U61.1
unnamed: 10K_R18.1, 30K_R18.1, U62.10
unnamed: 1NF_C19.1, 2K_R36.2, 10V_D36.2, U62.3
unnamed: 10V_D36.1, 10V_D37.1
unnamed: 2K_R37.1, U62.1, U62.2
unnamed: 330_R19.2, 510_R71.2, U62.7
unnamed: 2K_R37.2, 330_R19.1, U62.6
unnamed: 510_R71.1, 510_R72.1, U62.9
unnamed: 32K_R37.1, 100K_R37.2, U63.1
unnamed: 10K_R1.2, 32K_R13.2, 510_R21.1, U24.2
unnamed: 10K_R1.1, 30K_R1.1, U23.10
unnamed: 10K_R9.2, 32K_R31.2, 510_R55.1, U51.2
unnamed: 10K_R2.1, 30K_R2.1, U21.10
unnamed: 10K_R2.2, 32K_R12.2, 510_R18.1, U22.2
unnamed: 10K_R3.1, 30K_R3.1, U19.10
unnamed: 10K_R4.1, 30K_R4.1, U17.10
unnamed: 10K_R5.1, 30K_R5.1, U25.10
unnamed: 10K_R6.1, 30K_R6.1, U27.10
unnamed: 10K_R7.1, 30K_R7.1, U29.10
unnamed: 10K_R8.1, 30K_R8.1, U31.10
unnamed: 10K_R10.2, 32K_R30.2, 510_R52.1, U49.2
unnamed: 10K_R11.2, 32K_R29.2, 510_R49.1, U47.2
unnamed: 10K_R12.2, 32K_R28.2, 510_R46.1, U45.2
unnamed: 10K_R13.2, 32K_R32.2, 510_R58.1, U53.2
unnamed: 10K_R14.2, 32K_R33.2, 510_R61.1, U55.2
unnamed: 10K_R15.1, 30K_R15.1, U56.10
unnamed: 10K_R16.2, 32K_R35.2, 510_R67.1, U59.2
unnamed: 10K_R17.2, 32K_R36.2, 510_R70.1, U61.2
unnamed: 10K_R18.2, 32K_R37.2, 510_R73.1, U63.2
unnamed: 2K_R47.2, SCH_D43.C, SCH_D44.C
unnamed: 2K_R54.2, SCH_D57.C, SCH_D58.C
unnamed: 2K_R48.2, SCH_D45.C, SCH_D46.C
unnamed: 2K_R49.2, SCH_D47.C, SCH_D48.C
unnamed: 2K_R55.2, SCH_D59.C, SCH_D60.C
unnamed: 2K_R50.2, SCH_D49.C, SCH_D50.C
unnamed: 2K_R51.2, SCH_D51.C, SCH_D52.C
unnamed: 2K_R56.2, SCH_D61.C, SCH_D62.C
unnamed: 2K_R52.2, SCH_D53.C, SCH_D54.C
PA3: 3.3V_D24.C, 510_R72.2, J1.38, U43.6, U43.7, U62.8
PA4: J3.31, U64.10
PA5: J1.12, U64.12
PA6: 3.3V_D9.C, 510_R54.2, J1.14, U5.1, U5.2, U50.8
PA10: J1.34, U15.5, U19.12
PB3: J1.32, U64.5
PB6: 3.3V_D20.C, 510_R1.2, J1.18, SCH_D22.C
PB7: 3.3V_D21.C, 510_R76.2, J3.22, SCH_D23.C
PB8: 3.3V_D22.C, 510_R77.2, J1.04, SCH_D63.C
PB9: 3.3V_D23.C, 510_R78.2, J1.06, SCH_D64.C
PB14: 3.3V_D19.C, J1.27, U67.6, U67.7
PB15: J1.25, U15.3, U17.12
PC0: 3.3V_D16.C, 510_R66.2, J3.37, U6.13, U6.14, U58.8
PC6: J1.03, U64.3
PD11: J1.46, U16.3, U31.12
PD12: 3.3V_D2.C, 510_R17.2, J1.44, U2.6, U2.7, U21.8
PD13: 3.3V_D3.C, 510_R14.2, J1.42, U2.8, U2.9, U19.8
PD14: J1.45, U15.10, U21.12
PD15: 3.3V_D1.C, 510_R20.2, J1.47, U2.1, U2.2, U23.8
PE1: 3.3V_D18.C, J3.62, U67.1, U67.2
PE7: J1.43, U16.12, U25.12
PE8: J1.39, U16.10, U27.12
PE9: J1.51, U15.12, U23.12
PE12: 3.3V_D5.C, 510_R23.2, J1.50, U3.1, U3.2, U25.8
PE13: 3.3V_D6.C, 510_R26.2, J1.56, U3.6, U3.7, U27.8
PE14: 3.3V_D8.C, 510_R29.2, J1.52, U3.8, U3.9, U29.8
PE15: 3.3V_D7.C, 510_R32.2, J1.54, U3.13, U3.14, U31.8
PF6: 3.3V_D11.C, 510_R48.2, J3.10, U5.8, U5.9, U46.8
PF7: 3.3V_D12.C, 510_R45.2, J3.12, U5.13, U5.14, U44.8
PF8: 3.3V_D13.C, 510_R57.2, J3.53, U6.1, U6.2, U52.8
PF9: 3.3V_D14.C, 510_R60.2, J3.55, U6.6, U6.7, U54.8
PF10: 3.3V_D15.C, 510_R63.2, J1.41, U6.8, U6.9, U56.8
PF11: 3.3V_D10.C, 510_R51.2, J1.61, U5.6, U5.7, U48.8
PF14: 3.3V_D17.C, 510_R69.2, J1.49, U43.1, U43.2, U60.8
PF15: 3.3V_D4.C, 510_R11.2, J1.59, U2.13, U2.14, U17.8
PG6: J1.69, U16.5, U29.12
PWM_1: 2K_R55.1, J8.01
PWM_1_T: SCH_D61.A, U64.1, U64.2
PWM_2: 2K_R56.1, J8.03
PWM_2_T: SCH_D59.A, U64.6, U64.7
VIN: J3.23, U1.3

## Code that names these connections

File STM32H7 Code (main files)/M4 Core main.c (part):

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  __HAL_RCC_GPIOE_CLK_ENABLE();
  __HAL_RCC_GPIOD_CLK_ENABLE();

  /*Configure GPIO pin : PF15 */
  GPIO_InitStruct.Pin = GPIO_PIN_15;
  GPIO_InitStruct.Mode = GPIO_MODE_INPUT;
  GPIO_InitStruct.Pull = GPIO_NOPULL;
  HAL_GPIO_Init(GPIOF, &GPIO_InitStruct);

  /*Configure GPIO pins : PE12 PE13 PE14 PE15 */
  GPIO_InitStruct.Pin = GPIO_PIN_12|GPIO_PIN_13|GPIO_PIN_14|GPIO_PIN_15;
  GPIO_InitStruct.Mode = GPIO_MODE_INPUT;
  GPIO_InitStruct.Pull = GPIO_NOPULL;
  HAL_GPIO_Init(GPIOE, &GPIO_InitStruct);

  /*Configure GPIO pins : PD12 PD13 PD15 */
  GPIO_InitStruct.Pin = GPIO_PIN_12|GPIO_PIN_13|GPIO_PIN_15;
  GPIO_InitStruct.Mode = GPIO_MODE_INPUT;
  GPIO_InitStruct.Pull = GPIO_NOPULL;
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
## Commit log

2026-01-11 Capstone Documents
2026-01-11 Changing Documents to pdf
2026-02-24 Enhance README with images
    Added images to the README for better visualization.

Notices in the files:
STM32H7 Code (main files)/M4 Core main.c:
Copyright (c) 2025 STMicroelectronics.
All rights reserved.
This software is licensed under terms that can be found in the LICENSE file
parts and their libraries:
COPYRIGHT: Copyright (C) 2025 Ultra Librarian. All rights reserved.
